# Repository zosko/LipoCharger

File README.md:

# LipoCharger
Lipo / Li-ion charger

## Scheme

## Board

## Preview

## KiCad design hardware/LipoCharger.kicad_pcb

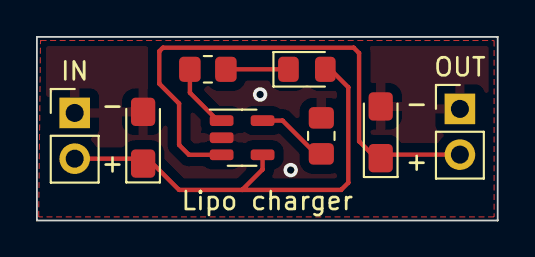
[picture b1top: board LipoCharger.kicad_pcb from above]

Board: 2 copper layers, 25.6 x 10.2 mm, 8 parts (0 on the bottom side), 6 nets.

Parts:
C1, C2: 4.7uF; CP_EIA-3216-18_Kemet-A_Pad1.58x1.35mm_HandSolder
D1: LED; LED_0805_2012Metric_Pad1.15x1.40mm_HandSolder
IN: Conn_01x02_Male; PinHeader_1x02_P2.54mm_Vertical
OUT: Conn_01x02_Male; PinHeader_1x02_P2.54mm_Vertical
R1: 2K; R_0805_2012Metric_Pad1.20x1.40mm_HandSolder
R2: 470; R_0805_2012Metric_Pad1.20x1.40mm_HandSolder
U1: MCP73831-2-OT; SOT-23-5

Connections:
GND: C1.2, C2.2, IN.1, OUT.1, R1.1, U1.2 (VSS)
unnamed: C1.1, D1.2 (A), IN.2, U1.4 (VDD)
unnamed: C2.1, OUT.2, U1.3 (VBAT)
unnamed: D1.1 (K), R2.2
unnamed: R1.2, U1.5 (PROG)
unnamed: R2.1, U1.1 (STAT)
